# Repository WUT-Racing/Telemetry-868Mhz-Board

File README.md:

# System Dwukanałowego Sniffera CAN - Płytka (Hardware)

## Opis projektu

Repozytorium zawiera projekt sprzętowy (hardware / PCB) dwukanałowego sniffera CAN, zaprojektowanego na potrzeby telemetrii bolidu Formuły Student.
Głównym zadaniem układu jest bezinwazyjny nasłuch (tryb _silent / bus monitoring_) dwóch niezależnych magistral CAN w pojeździe i przekazywanie zagregowanych ramek przez szybki interfejs UART do zewnętrznego modułu komunikacyjnego (np. modułu radiowego).

Układ został oparty o wydajny mikrokontroler **STM32G484RET6**. Na płytce przewidziano również dedykowany interfejs komunikacyjny dla modułu ESP32, który docelowo ma pełnić rolę nadrzędnego kontrolera filtrującego i konfigurującego.

> **Uwaga:** To repozytorium zawiera wyłącznie projekt płytki drukowanej (schematy, pliki Gerber, BOM). Oprogramowanie układowe (firmware) odpowiedzialne za formatowanie ramek CAN do 12-bajtowych rekordów binarnych znajduje się w osobnym repozytorium.

## Główne parametry sprzętowe

- **Mikrokontroler:** STM32G484RET6 (ARM Cortex-M4, taktowanie 170 MHz)
- **Interfejsy CAN:** 2x kanał sprzętowy dla magistrali Classical CAN (taktowanie do 1 Mbps)
- **Transceivery CAN:** 2x SN65HVD230DR
  - Zasilanie i logika 3.3V
  - Wbudowana terminacja magistrali 120 Ω
- **Interfejs telemetryczny (Radio):** USART2 z obsługą sprzętowej kontroli przepływu RTS/CTS (optymalizowany dla 921600 baud)
- **Interfejs konfiguracyjny (ESP32):** USART1
- **Sygnalizacja stanu:** Dioda LED wyprowadzona na pin PA5
- **Zasilanie układu:** 3.3V

## Pinout i połączenia zewnętrzne

### Interfejsy CAN (Transceivery)

| Funkcja STM32 | Pin  | Opis połączenia                                                                    |
| ------------- | ---- | ---------------------------------------------------------------------------------- |
| FDCAN1_RX     | PA11 | Odbiór ramek z sieci CAN1                                                          |
| FDCAN1_TX     | PA12 | Nadawanie CAN1 (w pierwszej wersji programowej sprzęt działa tylko jako odbiornik) |
| FDCAN2_RX     | PB12 | Odbiór ramek z sieci CAN2                                                          |
| FDCAN2_TX     | PB13 | Nadawanie CAN2                                                                     |

### Złącze wyjściowe telemetryczne (Moduł Radiowy)

Współpraca z modułem radiowym realizowana jest przez USART2:
| Funkcja | Pin STM32 | Opis |
|---|---|---|
| USART2_TX | PA2 | Główny strumień danych wysyłany przez DMA do modułu zewn. |
| USART2_RX | PA3 | Odbiór danych z modułu (opcjonalny) |

### Złącze modułu konfigurującego (ESP32)

Połączenie pomiędzy STM32 i ESP32 jest krzyżowe. Wymagane jest też połączenie masy.
| Funkcja STM32 | Pin | Podłączenie po stronie ESP32 |
|---|---|---|
| USART1_TX | PC4 | ESP32 RX |
| USART1_RX | PC5 | ESP32 TX |
| GND | GND | GND |

### Sygnalizacja statusu

| Funkcja    | Pin STM32 | Opis sprzętowy                                                                  |
| ---------- | --------- | ------------------------------------------------------------------------------- |
| LED_STATUS | PA5       | Dioda LED; stan wysoki na pinie załącza diodę (szeregowy rezystor 330Ω do GND). |

---

## Galeria PCB

## Uwagi montażowe i uruchomieniowe

1. **Terminacja CAN:** Płytka posiada zintegrowane rezystory terminujące 120Ω dla obydwu magistral CAN. Upewnij się co do topologii sieci w bolidzie, aby uniknąć zdublowanej terminacji w jednym węźle.
2. **Kontrola przepływu:** Złącze USART2 wspiera linie RTS/CTS. Jeśli podłączany zewnętrzny moduł radiowy nie posiada tych linii sprzętowych, zewrzyj lub skonfiguruj odpowiednio wejścia, aby nie blokować transmisji (zgodnie z ustawieniami peryferiów).
3. **Złącze SWD:** Na płytce wyprowadzono standardowe złącze SWD do programowania i debugowania mikrokontrolera STM32.

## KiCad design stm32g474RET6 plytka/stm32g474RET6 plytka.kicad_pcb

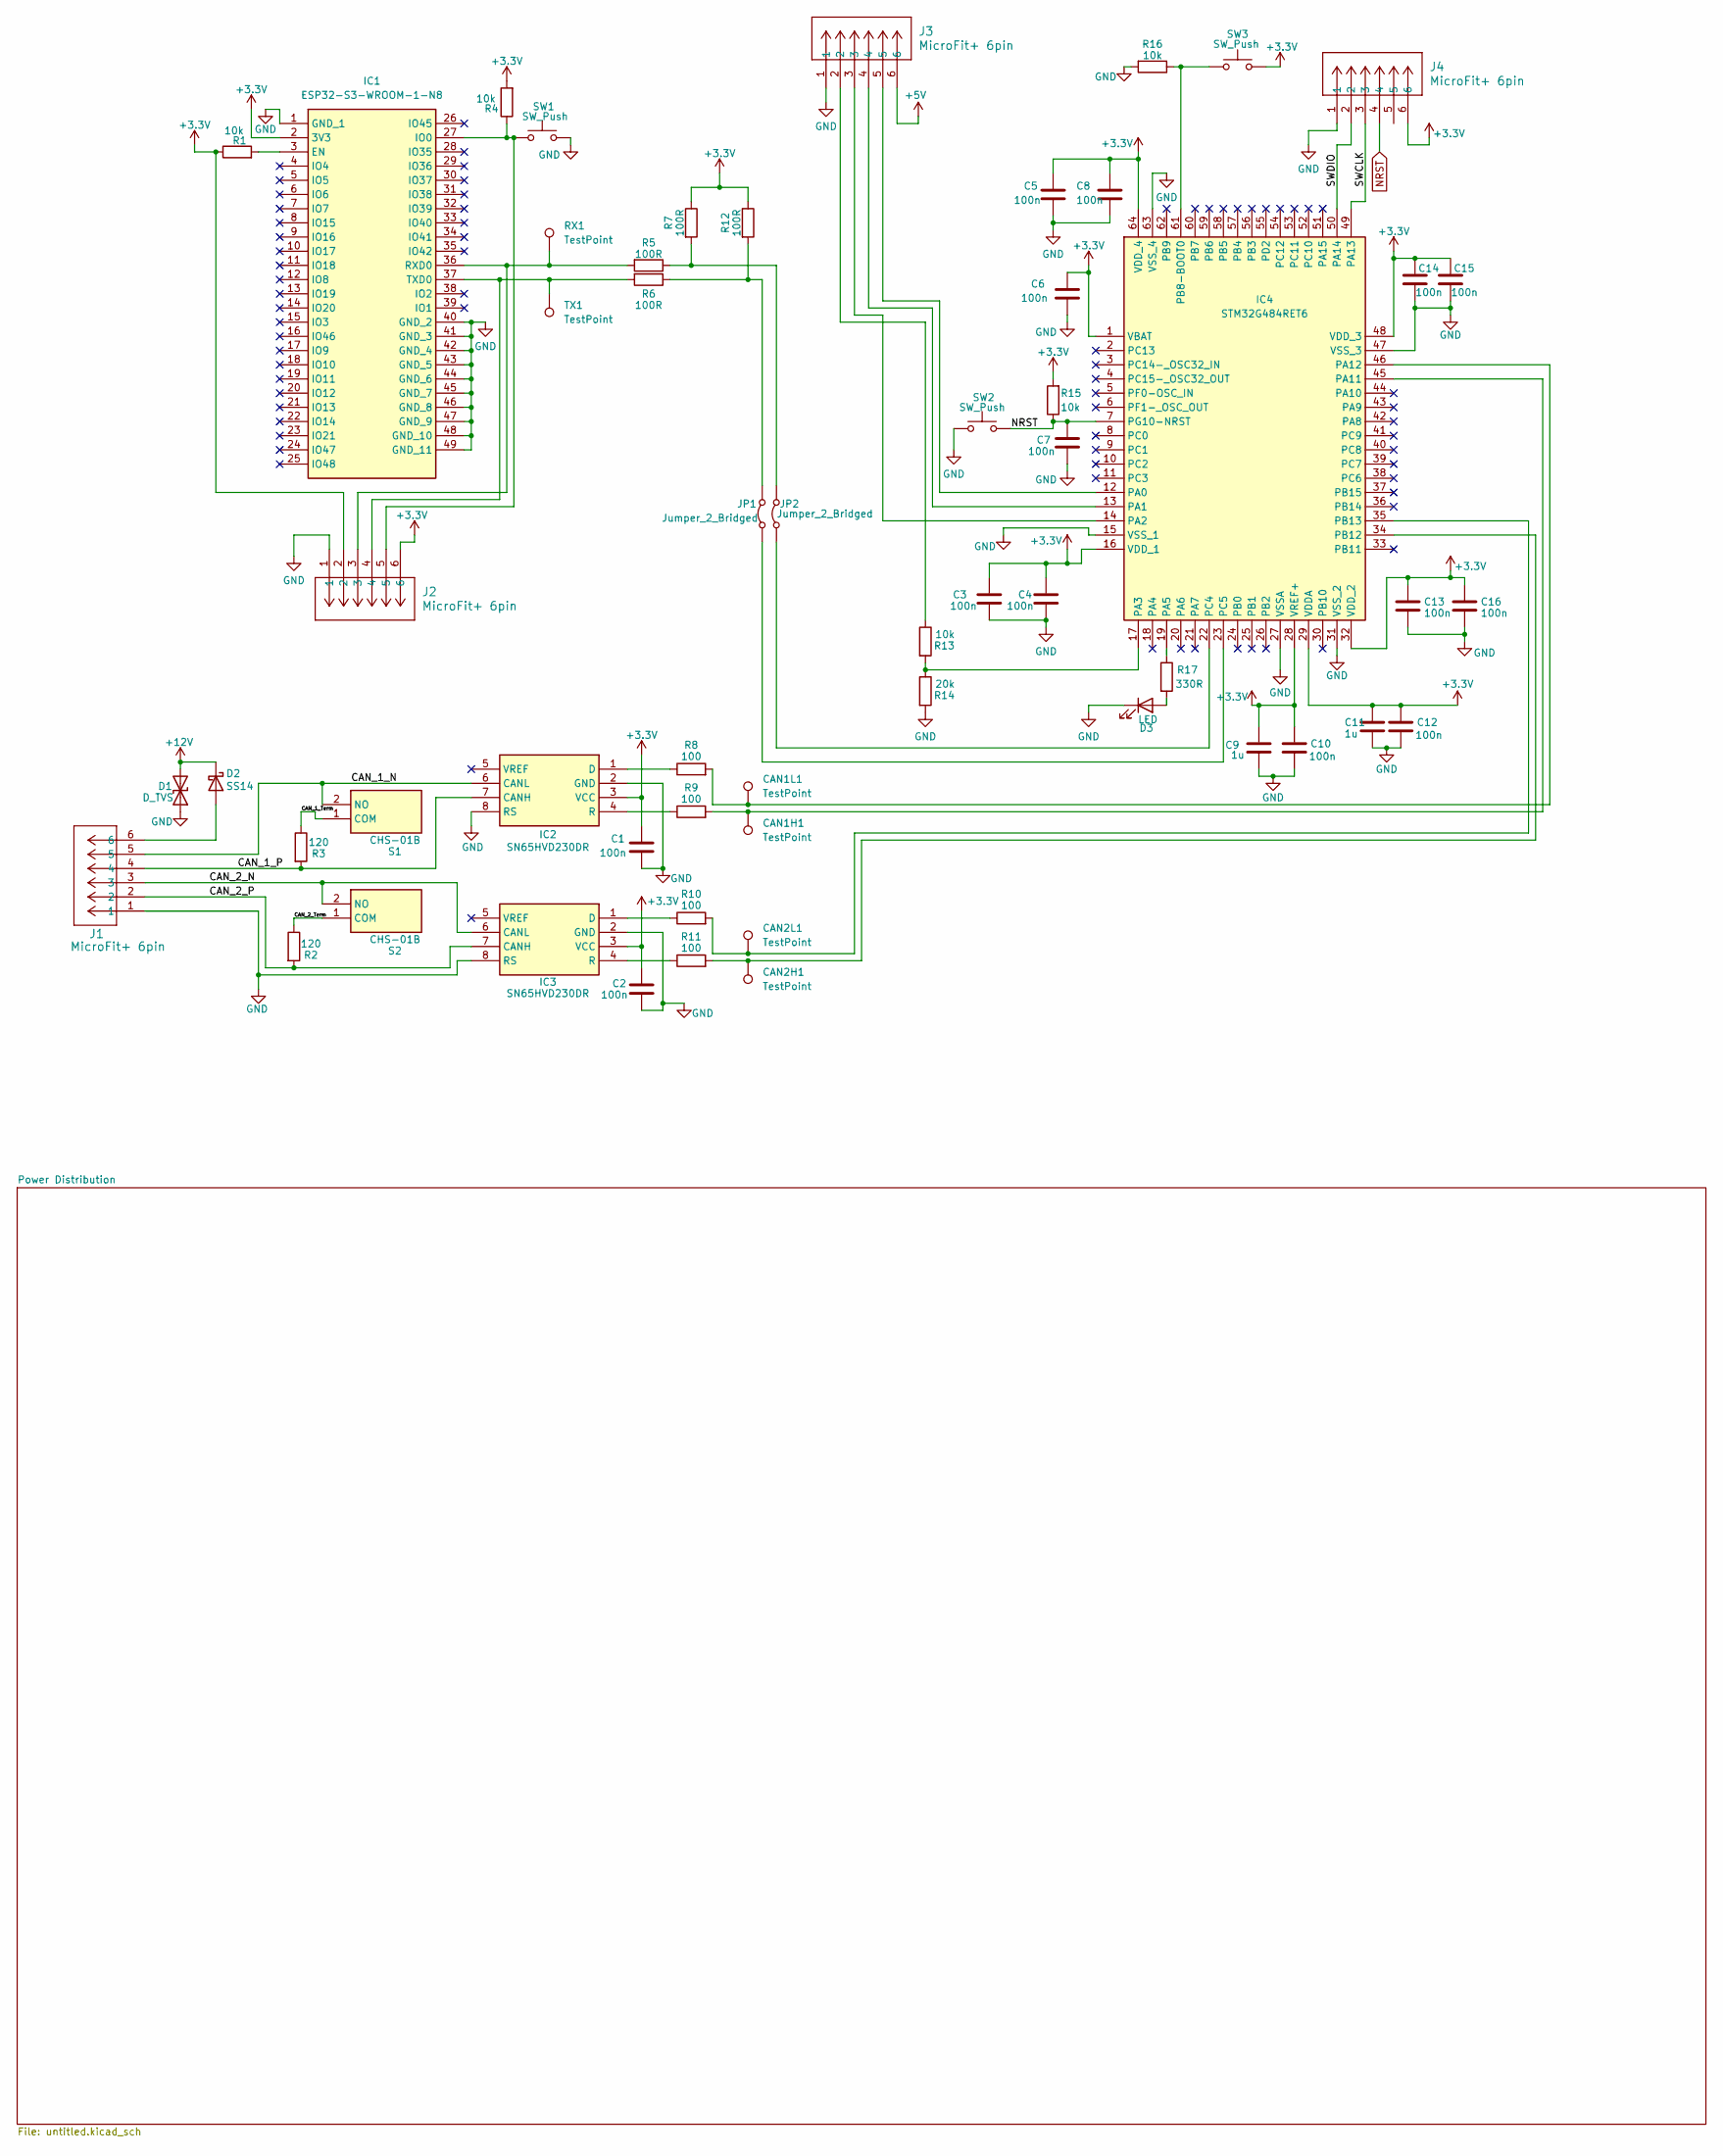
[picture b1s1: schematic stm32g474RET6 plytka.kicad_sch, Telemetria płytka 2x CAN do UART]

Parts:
C1, C2, C3, C4, C5, C6, C7, C8, C10, C12, C13, C14, C15, C16: 100n; C_0603_1608Metric_Pad1.08x0.95mm_HandSolder
C9, C11: 1u; C_0603_1608Metric_Pad1.08x0.95mm_HandSolder
CAN1H1, CAN1L1, CAN2H1, CAN2L1: TestPoint; TestPoint_THTPad_1.5x1.5mm_Drill0.7mm
D1: D_TVS; D_SMC
D2: SS14; D_SMA
D3: LED; LED_0603_1608Metric_Pad1.05x0.95mm_HandSolder
IC1: ESP32-S3-WROOM-1-N8; ESP32S3WROOM1N8R2; Mouser Part Number 356-ESP32-S3WROOM1N8
IC2, IC3: SN65HVD230DR; SOT127P600X175-8N; Mouser Part Number 595-SN65HVD230DR
IC4: STM32G484RET6; QFP50P1200X1200X160-64N; Mouser Part Number 511-STM32G484RET6
J1, J2, J3, J4: MicroFit+ 6pin; CONN_2125280000_06_MOL
JP1, JP2: Jumper_2_Bridged; PinHeader_1x02_P2.54mm_Vertical
R1, R4, R13, R15, R16: 10k; R_0603_1608Metric_Pad0.98x0.95mm_HandSolder
R2, R3: 120; R_0603_1608Metric_Pad0.98x0.95mm_HandSolder
R5, R6, R7, R12: 100R; R_0603_1608Metric_Pad0.98x0.95mm_HandSolder
R8, R9, R10, R11: 100; R_0603_1608Metric_Pad0.98x0.95mm_HandSolder
R14: 20k; R_0603_1608Metric_Pad0.98x0.95mm_HandSolder
R17: 330R; R_0603_1608Metric_Pad0.98x0.95mm_HandSolder
RX1: TestPoint; TestPoint_THTPad_1.5x1.5mm_Drill0.7mm
S1, S2: CHS-01B; CHS01TB; Mouser Part Number 229-CHS-01B
SW1, SW2, SW3: SW_Push; TS406643BK160SMTTR
TX1: TestPoint; TestPoint_THTPad_1.5x1.5mm_Drill0.7mm

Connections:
+3.3V: C1.1, C2.1, C3.1, C4.1, C5.1, C6.1, C8.1, C9.1, C10.1, C11.1, C12.1, C13.1, C14.1, C15.1, C16.1, IC1.2 (3V3), IC2.3 (VCC), IC3.3 (VCC), IC4.1 (VBAT), IC4.16 (VDD_1), IC4.28 (VREF+), IC4.29 (VDDA), IC4.32 (VDD_2), IC4.48 (VDD_3), IC4.64 (VDD_4), J2.2, J2.6, J4.6, R1.1, R4.2, R7.1, R12.1, R15.2, SW3.2; also elsewhere on the board
+5V: J3.6; also elsewhere on the board
+12V: D1.2 (A2), D2.1 (K); also elsewhere on the board
/CAN_1_N: IC2.6 (CANL), J1.5, S1.2 (NO)
/CAN_1_P: IC2.7 (CANH), J1.4, R3.2
/CAN_1_Term: R3.1, S1.1 (COM)
/CAN_2_N: IC3.6 (CANL), J1.3, S2.2 (NO)
/CAN_2_P: IC3.7 (CANH), J1.2, R2.2
/CAN_2_Term: R2.1, S2.1 (COM)
/SWCLK: IC4.49 (PA13), J4.3
/SWDIO: IC4.50 (PA14), J4.2
GND: C1.2, C2.2, C3.2, C4.2, C5.2, C6.2, C7.2, C8.2, C9.2, C10.2, C11.2, C12.2, C13.2, C14.2, C15.2, C16.2, D1.1 (A1), D3.1 (K), IC1.1 (GND_1), IC1.40 (GND_2), IC1.41 (GND_3), IC1.42 (GND_4), IC1.43 (GND_5), IC1.44 (GND_6), IC1.45 (GND_7), IC1.46 (GND_8), IC1.47 (GND_9), IC1.48 (GND_10), IC1.49 (GND_11), IC2.2 (GND), IC2.8 (RS), IC3.2 (GND), IC3.8 (RS), IC4.15 (VSS_1), IC4.27 (VSSA), IC4.31 (VSS_2), IC4.47 (VSS_3), IC4.63 (VSS_4), J1.1, J2.1, J3.1, J4.1, R14.2, R16.2, SW1.2, SW2.1; also elsewhere on the board
NRST: C7.1, IC4.7 (PG10-NRST), J4.4, R15.1, SW2.2
unnamed: D2.2 (A), J1.6
unnamed: D3.2 (A), R17.2
unnamed: IC1.3 (EN), R1.2
unnamed: IC1.27 (IO0), J2.5, R4.1, SW1.1
unnamed: IC1.36 (RXD0), J2.3, R5.2, RX1.1 (1_1)
unnamed: IC1.37 (TXD0), J2.4, R6.2, TX1.1 (1_1)
unnamed: IC2.1 (D), R8.1
unnamed: IC2.4 (R), R9.1
unnamed: IC3.1 (D), R10.1
unnamed: IC3.4 (R), R11.1
unnamed: IC4.12 (PA0), J3.5
unnamed: IC4.13 (PA1), J3.4
unnamed: IC4.14 (PA2), J3.3
unnamed: IC4.17 (PA3), R13.2, R14.1
unnamed: IC4.19 (PA5), R17.1
unnamed: CAN1H1.1 (1_1), IC4.45 (PA11), R9.2
unnamed: CAN1L1.1 (1_1), IC4.46 (PA12), R8.2
unnamed: IC4.61 (PB8-BOOT0), R16.1, SW3.1
unnamed: CAN2H1.1 (1_1), IC4.34 (PB12), R11.2
unnamed: CAN2L1.1 (1_1), IC4.35 (PB13), R10.2
unnamed: IC4.22 (PC4), JP2.1 (A)
unnamed: IC4.23 (PC5), JP1.1 (A)
unnamed: J3.2, R13.1
unnamed: JP1.2 (B), R6.1, R12.2
unnamed: JP2.2 (B), R5.1, R7.2

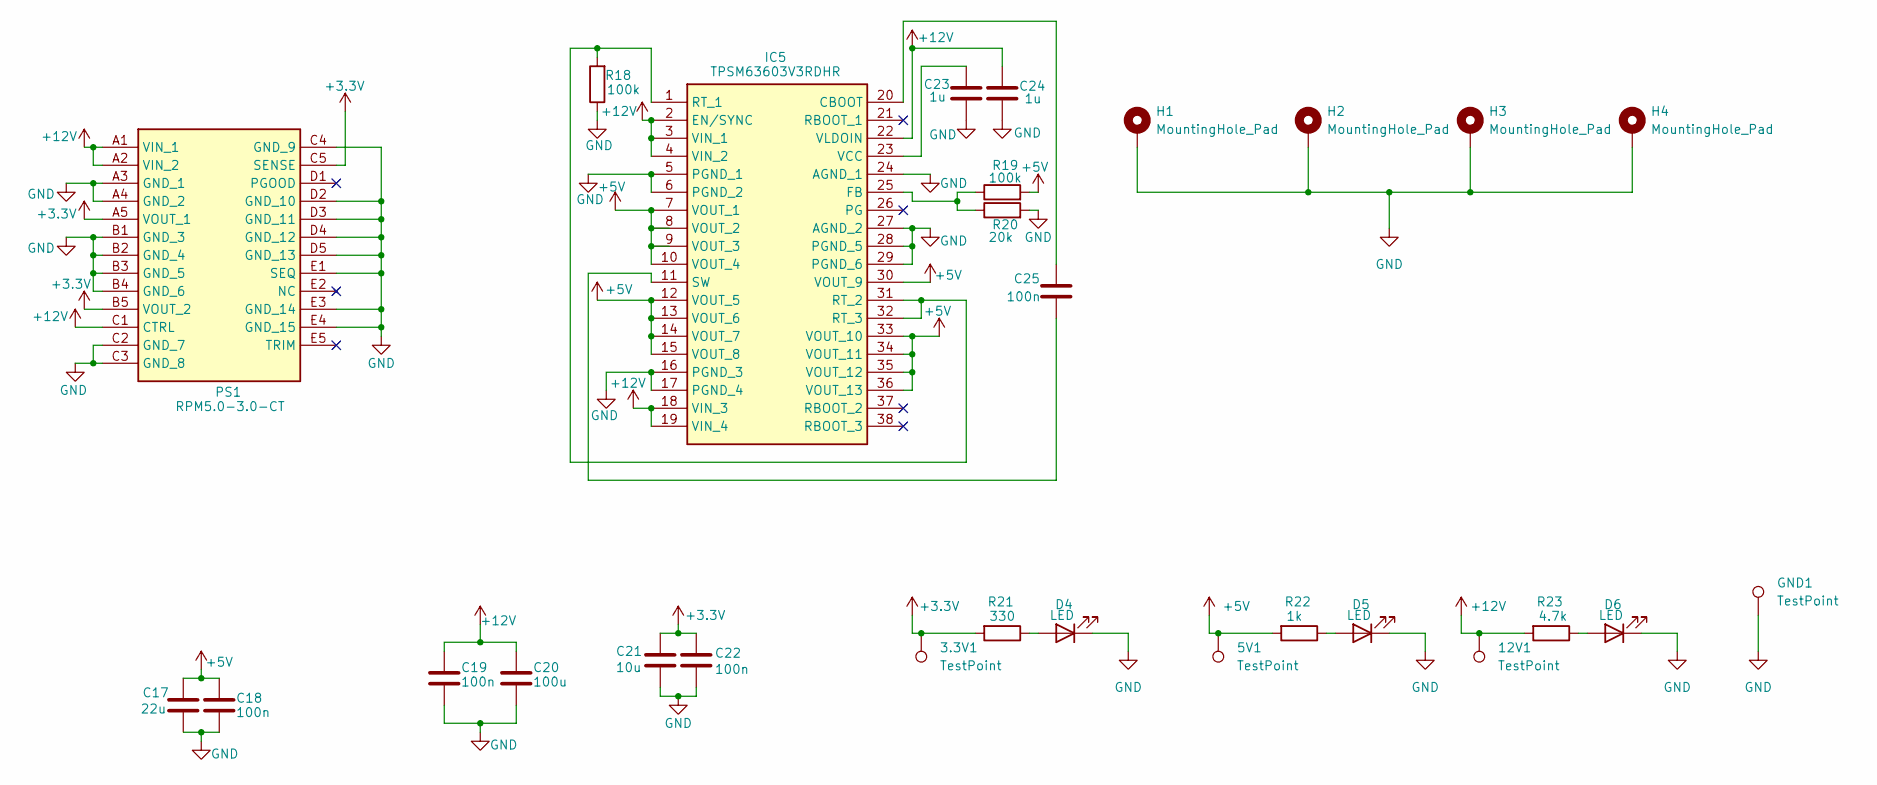
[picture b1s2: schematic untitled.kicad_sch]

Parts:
3.3V1, 5V1, 12V1: TestPoint; TestPoint_THTPad_1.5x1.5mm_Drill0.7mm
C17: 22u; C_0603_1608Metric_Pad1.08x0.95mm_HandSolder
C18, C19, C22, C25: 100n; C_0603_1608Metric_Pad1.08x0.95mm_HandSolder
C20: 100u; C_0603_1608Metric_Pad1.08x0.95mm_HandSolder
C21: 10u; C_0603_1608Metric_Pad1.08x0.95mm_HandSolder
C23, C24: 1u; C_0603_1608Metric_Pad1.08x0.95mm_HandSolder
D4, D5, D6: LED; LED_0603_1608Metric_Pad1.05x0.95mm_HandSolder
GND1: TestPoint; TestPoint_Loop_D2.50mm_Drill1.0mm
H1, H2, H3, H4: MountingHole_Pad; MountingHole_3.2mm_M3_DIN965_Pad
IC5: TPSM63603V3RDHR; TPSM63603EXTRDHR; Mouser Part Number 595-TPSM63603V3RDHR
PS1: RPM5.0-3.0-CT; RPM5030CT; Mouser Part Number 919-RPM5.0-3.0-CT
R18, R19: 100k; R_0603_1608Metric_Pad0.98x0.95mm_HandSolder
R20: 20k; R_0603_1608Metric_Pad0.98x0.95mm_HandSolder
R21: 330; R_0603_1608Metric_Pad0.98x0.95mm_HandSolder
R22: 1k; R_0603_1608Metric_Pad0.98x0.95mm_HandSolder
R23: 4.7k; R_0603_1608Metric_Pad0.98x0.95mm_HandSolder

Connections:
+3.3V: 3.3V1.1 (1_1), C21.1, C22.1, PS1.A5 (VOUT_1), PS1.B5 (VOUT_2), PS1.C5 (SENSE), R21.2; also elsewhere on the board
+5V: 5V1.1 (1_1), C17.1, C18.1, IC5.7 (VOUT_1), IC5.8 (VOUT_2), IC5.9 (VOUT_3), IC5.10 (VOUT_4), IC5.12 (VOUT_5), IC5.13 (VOUT_6), IC5.14 (VOUT_7), IC5.15 (VOUT_8), IC5.30 (VOUT_9), IC5.33 (VOUT_10), IC5.34 (VOUT_11), IC5.35 (VOUT_12), IC5.36 (VOUT_13), R19.2, R22.2; also elsewhere on the board
+12V: 12V1.1 (1_1), C19.1, C20.1, C24.1, IC5.2 (EN/SYNC), IC5.3 (VIN_1), IC5.4 (VIN_2), IC5.18 (VIN_3), IC5.19 (VIN_4), IC5.22 (VLDOIN), PS1.A1 (VIN_1), PS1.A2 (VIN_2), PS1.C1 (CTRL), R23.2; also elsewhere on the board
GND: C17.2, C18.2, C19.2, C20.2, C21.2, C22.2, C23.2, C24.2, D4.1 (K), D5.1 (K), D6.1 (K), GND1.1 (1_1), H1.1 (1_1), H2.1 (1_1), H3.1 (1_1), H4.1 (1_1), IC5.5 (PGND_1), IC5.6 (PGND_2), IC5.16 (PGND_3), IC5.17 (PGND_4), IC5.24 (AGND_1), IC5.27 (AGND_2), IC5.28 (PGND_5), IC5.29 (PGND_6), PS1.A3 (GND_1), PS1.A4 (GND_2), PS1.B1 (GND_3), PS1.B2 (GND_4), PS1.B3 (GND_5), PS1.B4 (GND_6), PS1.C2 (GND_7), PS1.C3 (GND_8), PS1.C4 (GND_9), PS1.D2 (GND_10), PS1.D3 (GND_11), PS1.D4 (GND_12), PS1.D5 (GND_13), PS1.E1 (SEQ), PS1.E3 (GND_14), PS1.E4 (GND_15), R18.1, R20.2; also elsewhere on the board
unnamed: D4.2 (A), R21.1
unnamed: D5.2 (A), R22.1
unnamed: D6.2 (A), R23.1
unnamed: C25.1, IC5.20 (CBOOT)
unnamed: IC5.25 (FB), R19.1, R20.1
unnamed: IC5.1 (RT_1), IC5.31 (RT_2), IC5.32 (RT_3), R18.2
unnamed: C25.2, IC5.11 (SW)
unnamed: C23.1, IC5.23 (VCC)

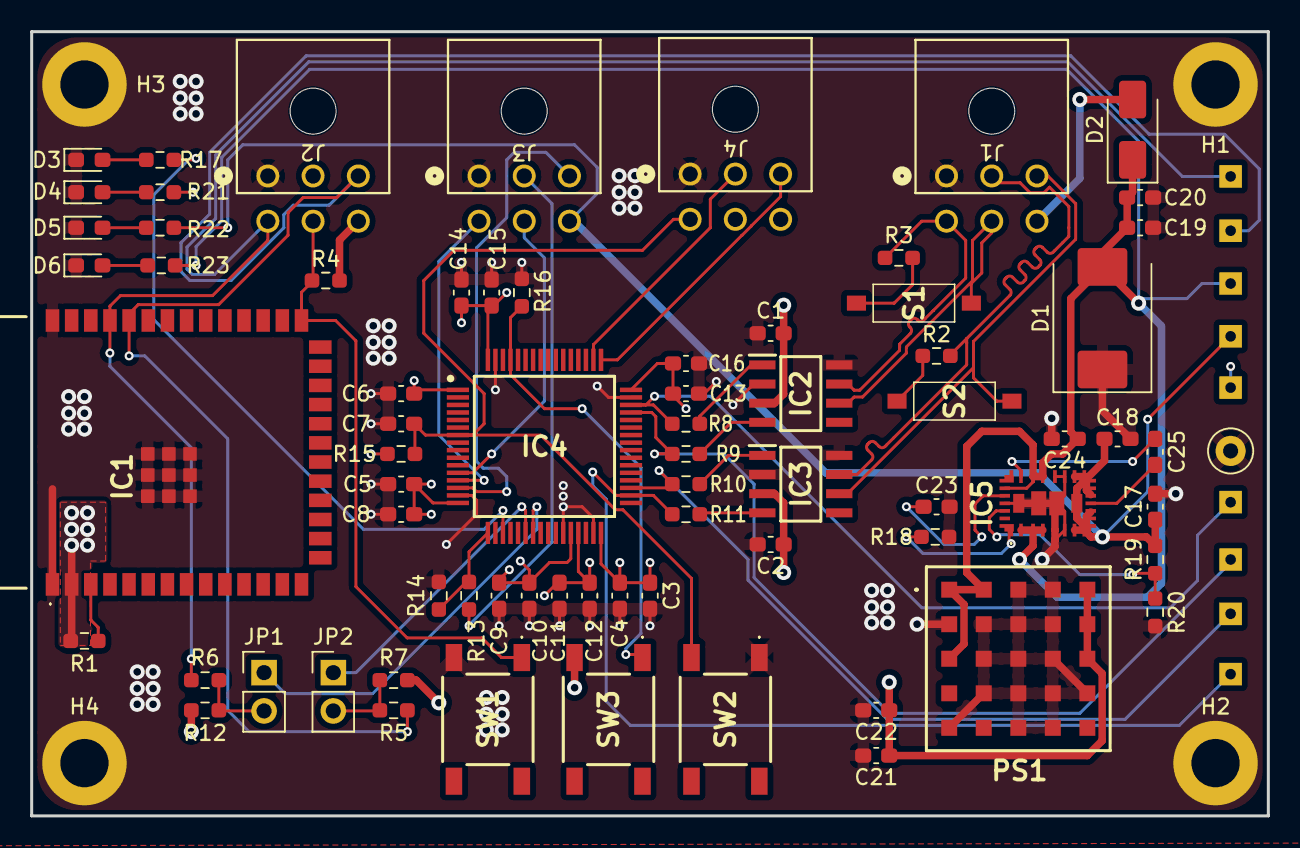
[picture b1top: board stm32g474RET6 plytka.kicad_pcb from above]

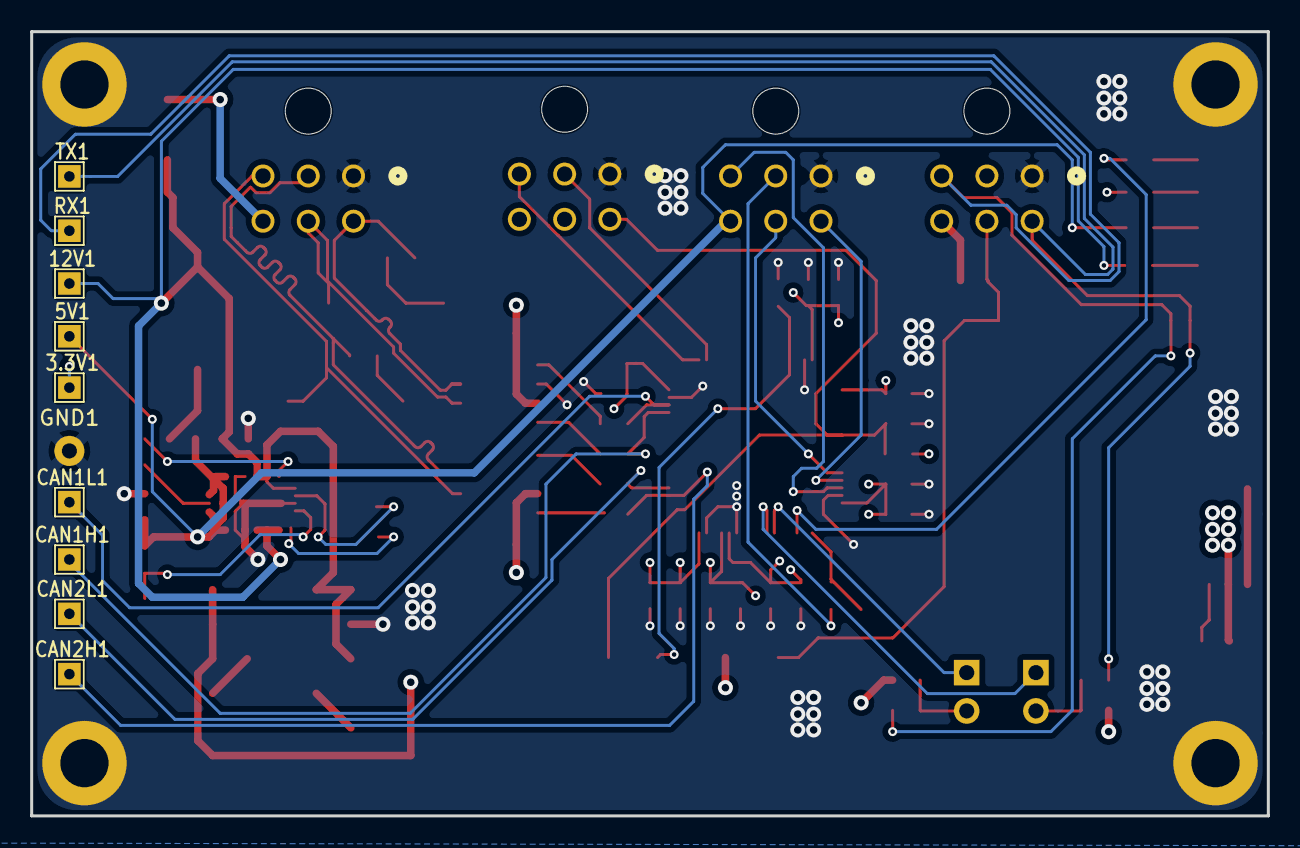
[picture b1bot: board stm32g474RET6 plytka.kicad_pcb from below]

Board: 4 copper layers, 82.0 x 52.0 mm, 85 parts (9 on the bottom side), 46 nets.
